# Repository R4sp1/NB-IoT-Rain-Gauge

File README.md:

# Návrh přesného srážkoměru s možností real-time odečtu

## Zadání
V teoretické části prostudujte principy měření objemu srážek. Prostudujte současné možnosti využití LPWAN sítí pro přenos naměřených hodnot. Na základě průzkumu dostupných řešení vyberte vhodnou metodu a měřicí modul pro přesné stanovení míry srážek. Současně vyberte vhodné komunikační řešení, které umožní real-time přenos naměřených hodnot. Výstupem semestrální práce je návrh a sestrojení zařízení pro přesné měření srážek s možností odesílání naměřených hodnot na server v reálném čase.

[Odkaz na práci](https://www.vut.cz/studenti/zav-prace/detail/151055 "Záverečné práce na VUT")

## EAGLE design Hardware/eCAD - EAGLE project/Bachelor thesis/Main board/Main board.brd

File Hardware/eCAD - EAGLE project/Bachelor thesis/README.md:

# eCAD files
This subfolder contains project files from EAGLE eCAD software. The main design is located in folder: [Main board](https://github.com/R4sp1/NB-IoT-Rain-Gauge/tree/main/Hardware/eCAD%20-%20EAGLE%20project/Bachelor%20thesis/Main%20board).

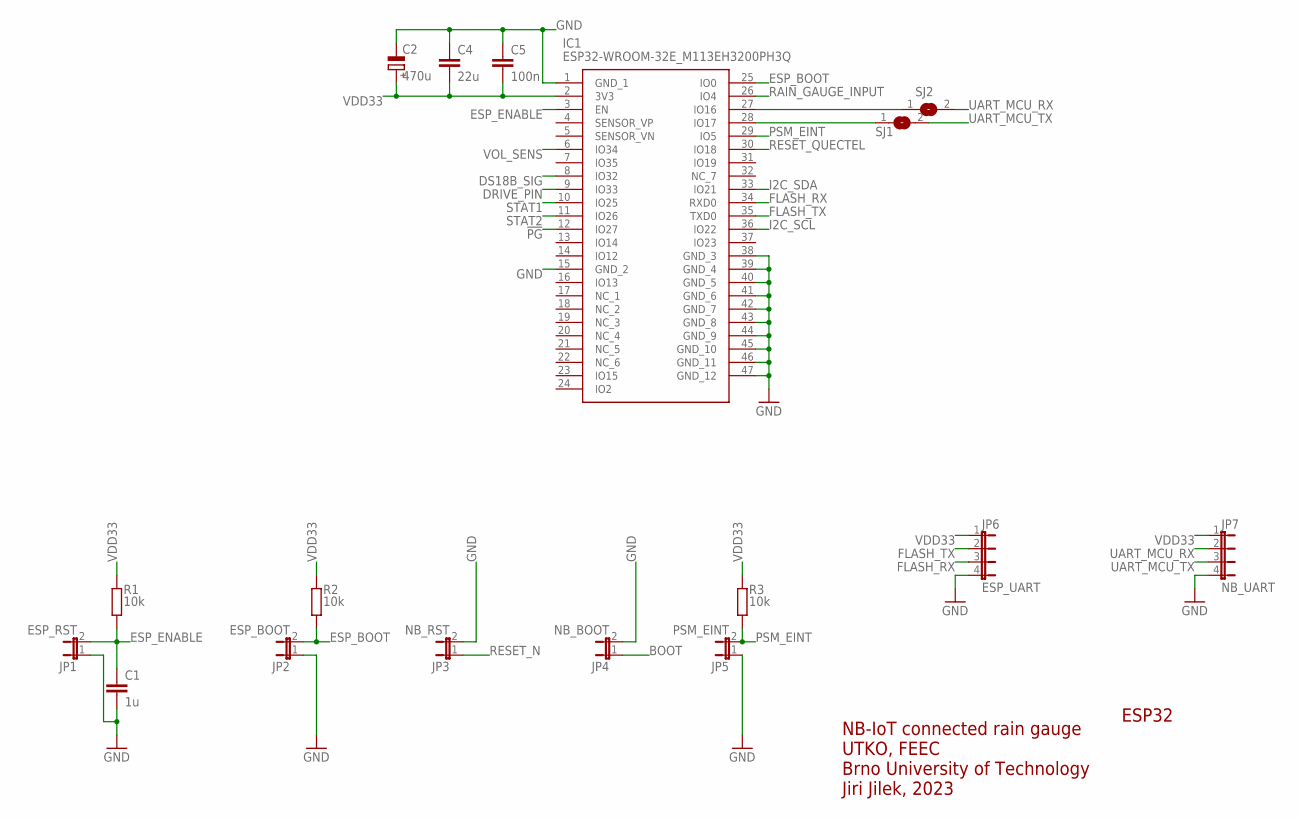
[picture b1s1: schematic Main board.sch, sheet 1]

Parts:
C1: 1u; C0603
C2: 470u; PANASONIC_D
C4: 22u; C0603
C5: 100n; C0603
IC1: ESP32-WROOM-32E_M113EH3200PH3Q; ESP32WROOM32EM113EH3200PH3Q0
JP1: ESP_RST; JP1
JP2: ESP_BOOT; JP1
JP3: NB_RST; JP1
JP4: NB_BOOT; JP1
JP5: PSM_EINT; JP1
JP6: ESP_UART; JP4
JP7: NB_UART; JP4
R1, R2, R3: 10k; R0603
SJ1, SJ2: SJ

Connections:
!PG: IC1.12 (IO27); also elsewhere on the board
BOOT: JP4.1; also elsewhere on the board
DRIVE_PIN: IC1.9 (IO33); also elsewhere on the board
DS18B_SIG: IC1.8 (IO32); also elsewhere on the board
ESP_BOOT: IC1.25 (IO0), JP2.2, R2.1
ESP_ENABLE: C1.1, IC1.3 (EN), JP1.2, R1.1
FLASH_RX: IC1.34 (RXD0), JP6.3
FLASH_TX: IC1.35 (TXD0), JP6.2
GND: C1.2, C2.-, C4.1, C5.1, IC1.1 (GND_1), IC1.15 (GND_2), IC1.38 (GND_3), IC1.39 (GND_4), IC1.40 (GND_5), IC1.41 (GND_6), IC1.42 (GND_7), IC1.43 (GND_8), IC1.44 (GND_9), IC1.45 (GND_10), IC1.46 (GND_11), IC1.47 (GND_12), JP1.1, JP2.1, JP3.2, JP4.2, JP5.1, JP6.4, JP7.4; also elsewhere on the board
I2C_SCL: IC1.36 (IO22); also elsewhere on the board
I2C_SDA: IC1.33 (IO21); also elsewhere on the board
unnamed: IC1.27 (IO16), SJ2.1
unnamed: IC1.28 (IO17), SJ1.1
PSM_EINT: IC1.29 (IO5), JP5.2, R3.1; also elsewhere on the board
RAIN_GAUGE_INPUT: IC1.26 (IO4); also elsewhere on the board
RESET_N: JP3.1; also elsewhere on the board
RESET_QUECTEL: IC1.30 (IO18); also elsewhere on the board
STAT1: IC1.10 (IO25); also elsewhere on the board
STAT2: IC1.11 (IO26); also elsewhere on the board
UART_MCU_RX: JP7.2, SJ2.2; also elsewhere on the board
UART_MCU_TX: JP7.3, SJ1.2; also elsewhere on the board
VDD33: C2.+, C4.2, C5.2, IC1.2 (3V3), JP6.1, JP7.1, R1.2, R2.2, R3.2; also elsewhere on the board
VOL_SENS: IC1.6 (IO34); also elsewhere on the board

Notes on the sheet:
ESP32
NB-IoT connected rain gauge UTKO, FEEC Brno University of Technology Jiri Jilek, 2023

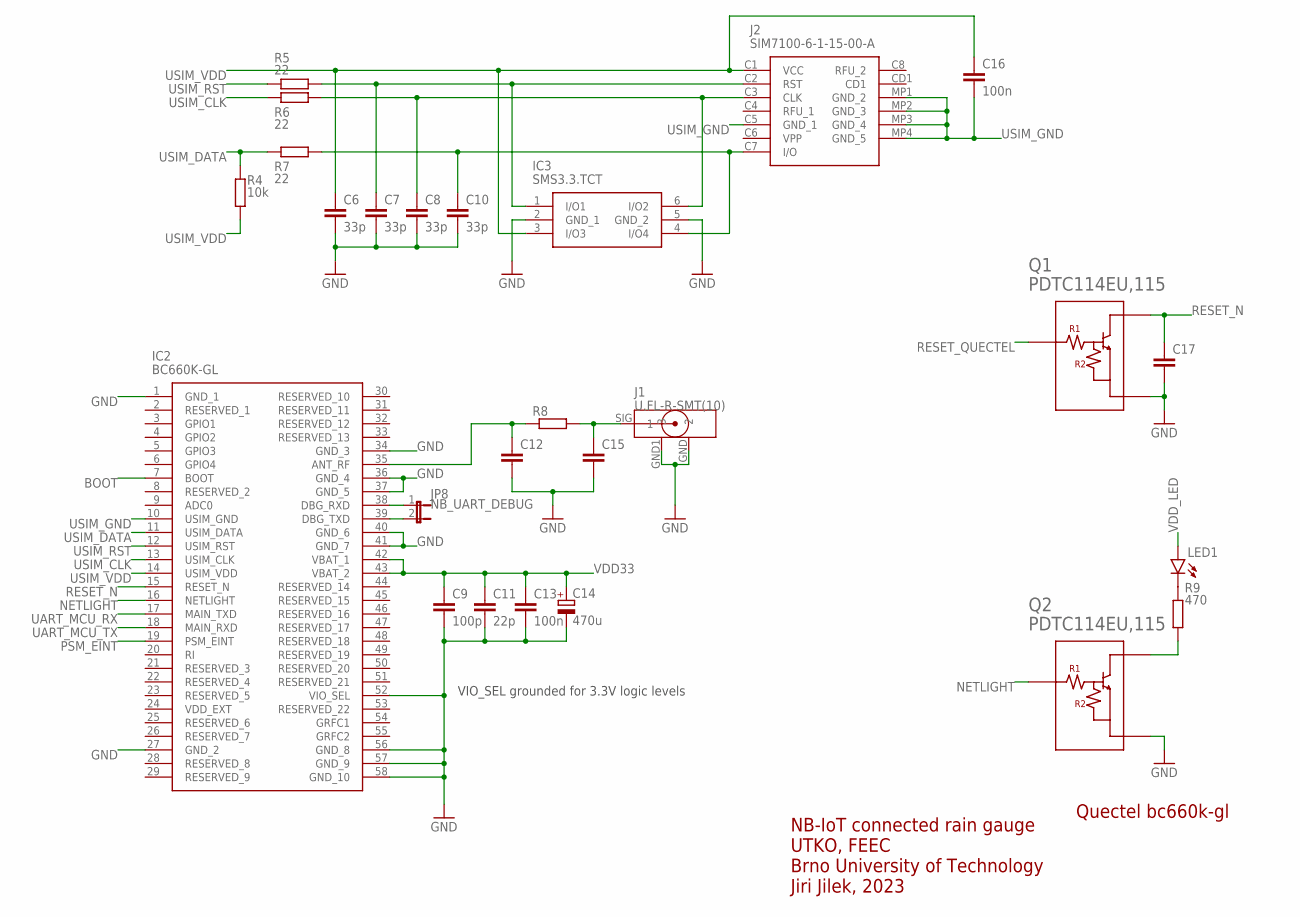
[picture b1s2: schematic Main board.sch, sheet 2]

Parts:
C6, C7, C8, C10: 33p; C0603
C9: 100p; C0603
C11: 22p; C0603
C12, C15, C17: C-EUC0603; C0603
C13, C16: 100n; C0603
C14: 470u; PANASONIC_D
IC2: BC660K-GL; BC660KGL
IC3: SMS3.3.TCT; SOT95P280X145-6N
J1: U.FL-R-SMT(10)
J2: SIM7100-6-1-15-00-A; SIM7100611500A
JP8: NB_UART_DEBUG; JP1
LED1: NETSTAT; CHIPLED_0805
Q1, Q2: PDTC114EU,115; SOT65P210X110-3N
R4: 10k; R0603
R5, R6, R7: 22; R0603
R8: R-EU_R0603; R0603
R9: 470; R0603

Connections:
BOOT: IC2.7 (BOOT); also elsewhere on the board
GND: C6.2, C7.2, C8.2, C9.2, C10.2, C11.2, C12.2, C13.2, C14.-, C15.2, C17.2, IC2.1 (GND_1), IC2.27 (GND_2), IC2.34 (GND_3), IC2.36 (GND_4), IC2.37 (GND_5), IC2.40 (GND_6), IC2.41 (GND_7), IC2.52 (VIO_SEL), IC2.56 (GND_8), IC2.57 (GND_9), IC2.58 (GND_10), IC3.2 (GND_1), IC3.5 (GND_2), J1.GND (2), J1.GND1 (3), Q1.2 (GND), Q2.2 (GND); also elsewhere on the board
unnamed: IC2.38 (DBG_RXD), JP8.1
unnamed: IC2.39 (DBG_TXD), JP8.2
unnamed: LED1.C, R9.2
unnamed: Q2.3 (OUTPUT), R9.1
unnamed: C12.1, IC2.35 (ANT_RF), R8.1
unnamed: C15.1, J1.SIG (1), R8.2
unnamed: C7.1, IC3.1 (I/O1), J2.C2 (RST), R5.2
unnamed: C8.1, IC3.6 (I/O2), J2.C3 (CLK), R6.2
unnamed: C10.1, IC3.4 (I/O4), J2.C7 (I/O), R7.2
NETLIGHT: IC2.16 (NETLIGHT), Q2.1 (INPUT)
PSM_EINT: IC2.19 (PSM_EINT); also elsewhere on the board
RESET_N: C17.1, IC2.15 (RESET_N), Q1.3 (OUTPUT); also elsewhere on the board
RESET_QUECTEL: Q1.1 (INPUT); also elsewhere on the board
UART_MCU_RX: IC2.17 (MAIN_TXD); also elsewhere on the board
UART_MCU_TX: IC2.18 (MAIN_RXD); also elsewhere on the board
USIM_CLK: IC2.13 (USIM_CLK), R6.1
USIM_DATA: IC2.11 (USIM_DATA), R4.2, R7.1
USIM_GND: C16.2, IC2.10 (USIM_GND), J2.C5 (GND_1), J2.MP1 (GND_2), J2.MP2 (GND_3), J2.MP3 (GND_4), J2.MP4 (GND_5)
USIM_RST: IC2.12 (USIM_RST), R5.1
USIM_VDD: C6.1, C16.1, IC2.14 (USIM_VDD), IC3.3 (I/O3), J2.C1 (VCC), R4.1
VDD33: C9.1, C11.1, C13.1, C14.+, IC2.42 (VBAT_1), IC2.43 (VBAT_2); also elsewhere on the board
VDD_LED: LED1.A; also elsewhere on the board

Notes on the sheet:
Quectel bc660k-gl
VIO_SEL grounded for 3.3V logic levels
NB-IoT connected rain gauge UTKO, FEEC Brno University of Technology Jiri Jilek, 2023

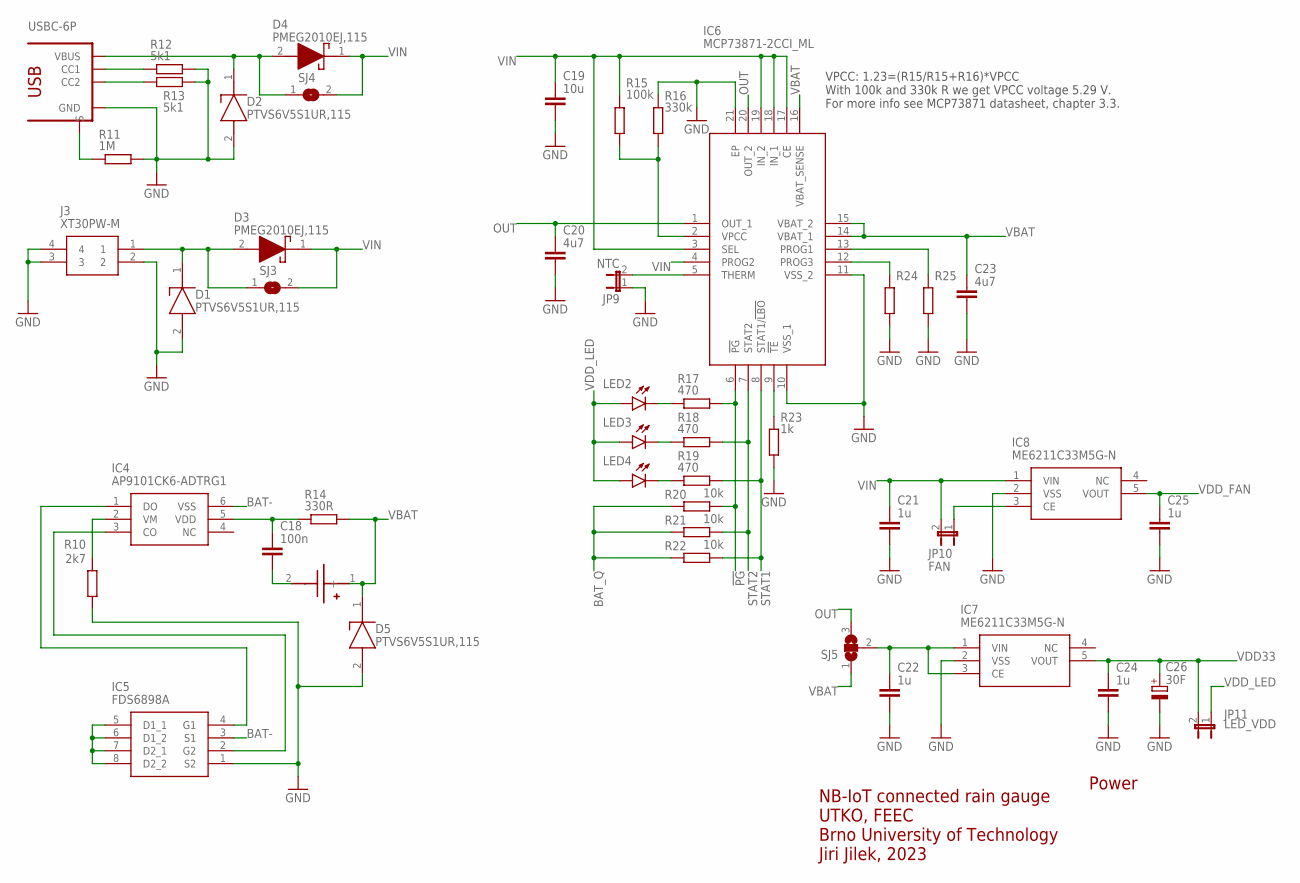
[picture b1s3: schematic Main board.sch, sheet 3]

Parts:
$3_29_$_2023-03-21_17-43-41: USBC-6P; USCX-06FX-XXMX-01
$3_30_$_2023-03-21_17-43-41: BLOSSOM-BLM-18650-1PCS
C18: 100n; C0603
C19: 10u; C0603
C20, C23: 4u7; C0603
C21, C22, C24, C25: 1u; C0603
C26: 30F; E5-10,5
D1, D2, D5: PTVS6V5S1UR,115; SOD123W
D3, D4: PMEG2010EJ,115; SODFL2512X80N
IC4: AP9101CK6-ADTRG1; SOT95P285X140-6N
IC5: FDS6898A; SOIC127P600X175-8N
IC6: MCP73871-2CCI_ML; QFN50P400X400X100-21N
IC7, IC8: ME6211C33M5G-N; SOT95P270X145-5N
J3: XT30PW-M; XT30PWM
JP9: NTC; JP1
JP10: FAN; JP1
JP11: LED_VDD; JP1
LED2: !PG; CHIPLED_0805
LED3: STAT2; CHIPLED_0805
LED4: STAT1; CHIPLED_0805
R10: 2k7; R0805
R11: 1M; R0603
R12, R13: 5k1; R0603
R14: 330R; R0603
R15: 100k; R0805
R16: 330k; R0805
R17, R18, R19: 470; R0603
R20, R21, R22: 10k; R0603
R23: 1k; R0603
R24, R25: R-EU_R0805; R0805
SJ3, SJ4: SJ
SJ5: SJ2W; SJ_2

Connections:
!PG: IC6.6 (!PG), R17.2, R20.2; also elsewhere on the board
!TE1: IC6.9 (!TE), R23.1
BAT-: $3_30_$_2023-03-21_17-43-41.2 (-), C18.2, IC4.6 (VSS), IC5.3 (S1)
BAT_Q: R20.1, R21.1, R22.1; also elsewhere on the board
CC3: $3_29_$_2023-03-21_17-43-41.CC2, R13.1
CC4: $3_29_$_2023-03-21_17-43-41.CC1, R12.1
DRAIN1: IC5.5 (D1_1), IC5.6 (D1_2), IC5.7 (D2_1), IC5.8 (D2_2)
G3: IC4.1 (DO), IC5.4 (G1)
G4: IC4.3 (CO), IC5.2 (G2)
GND: $3_29_$_2023-03-21_17-43-41.GND1 (GND), $3_29_$_2023-03-21_17-43-41.GND2 (GND), C19.2, C20.2, C21.2, C22.2, C23.2, C24.2, C25.2, C26.-, D1.2 (A), D2.2 (A), D5.2 (A), IC5.1 (S2), IC6.10 (VSS_1), IC6.11 (VSS_2), IC6.21 (EP), IC7.2 (VSS), IC8.2 (VSS), J3.2, J3.3, J3.4, JP9.1, R10.1, R11.2, R12.2, R13.2, R16.2, R23.2, R24.2, R25.2; also elsewhere on the board
unnamed: C18.1, IC4.5 (VDD), R14.1
unnamed: IC8.3 (CE), JP10.1
unnamed: LED2.C, R17.1
unnamed: LED3.C, R18.1
unnamed: LED4.C, R19.1
OUT: C20.1, IC6.1 (OUT_1), IC6.20 (OUT_2), SJ5.3
PROG1: IC6.13 (PROG1), R25.1
PROG3: IC6.12 (PROG3), R24.1
PV_IN1: D1.1 (K), D3.2 (A), J3.1, SJ3.1
S1: $3_29_$_2023-03-21_17-43-41.SHIELD1 (S), $3_29_$_2023-03-21_17-43-41.SHIELD2 (S), $3_29_$_2023-03-21_17-43-41.SHIELD3 (S), $3_29_$_2023-03-21_17-43-41.SHIELD4 (S), R11.1
STAT1: IC6.8 (STAT1/!LBO), R19.2, R22.2; also elsewhere on the board
STAT2: IC6.7 (STAT2), R18.2, R21.2; also elsewhere on the board
THERM1: IC6.5 (THERM), JP9.2
VBAT: $3_30_$_2023-03-21_17-43-41.1 (+), C23.1, D5.1 (K), IC6.14 (VBAT_1), IC6.15 (VBAT_2), IC6.16 (VBAT_SENSE), R14.2, SJ5.1; also elsewhere on the board
VBUS1: $3_29_$_2023-03-21_17-43-41.VBUS1 (VBUS), $3_29_$_2023-03-21_17-43-41.VBUS2 (VBUS), D2.1 (K), D4.2 (A), SJ4.1
VDD33: C24.1, C26.+, IC7.5 (VOUT), JP11.2; also elsewhere on the board
VDD_FAN: C25.1, IC8.5 (VOUT); also elsewhere on the board
VDD_LED: JP11.1, LED2.A, LED3.A, LED4.A; also elsewhere on the board
VIN: C19.1, C21.1, D3.1 (K), D4.1 (K), IC6.3 (SEL), IC6.4 (PROG2), IC6.17 (CE), IC6.18 (IN_1), IC6.19 (IN_2), IC8.1 (VIN), JP10.2, R15.2, SJ3.2, SJ4.2
VIN_LDO: C22.1, IC7.1 (VIN), IC7.3 (CE), SJ5.2
VM1: IC4.2 (VM), R10.2
VPCC1: IC6.2 (VPCC), R15.1, R16.1

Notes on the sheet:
Power
VPCC: 1.23=(R15/R15+R16)*VPCC With 100k and 330k R we get VPCC voltage 5.29 V. For more info see MCP73871 datasheet, chapter 3.3.
NB-IoT connected rain gauge UTKO, FEEC Brno University of Technology Jiri Jilek, 2023

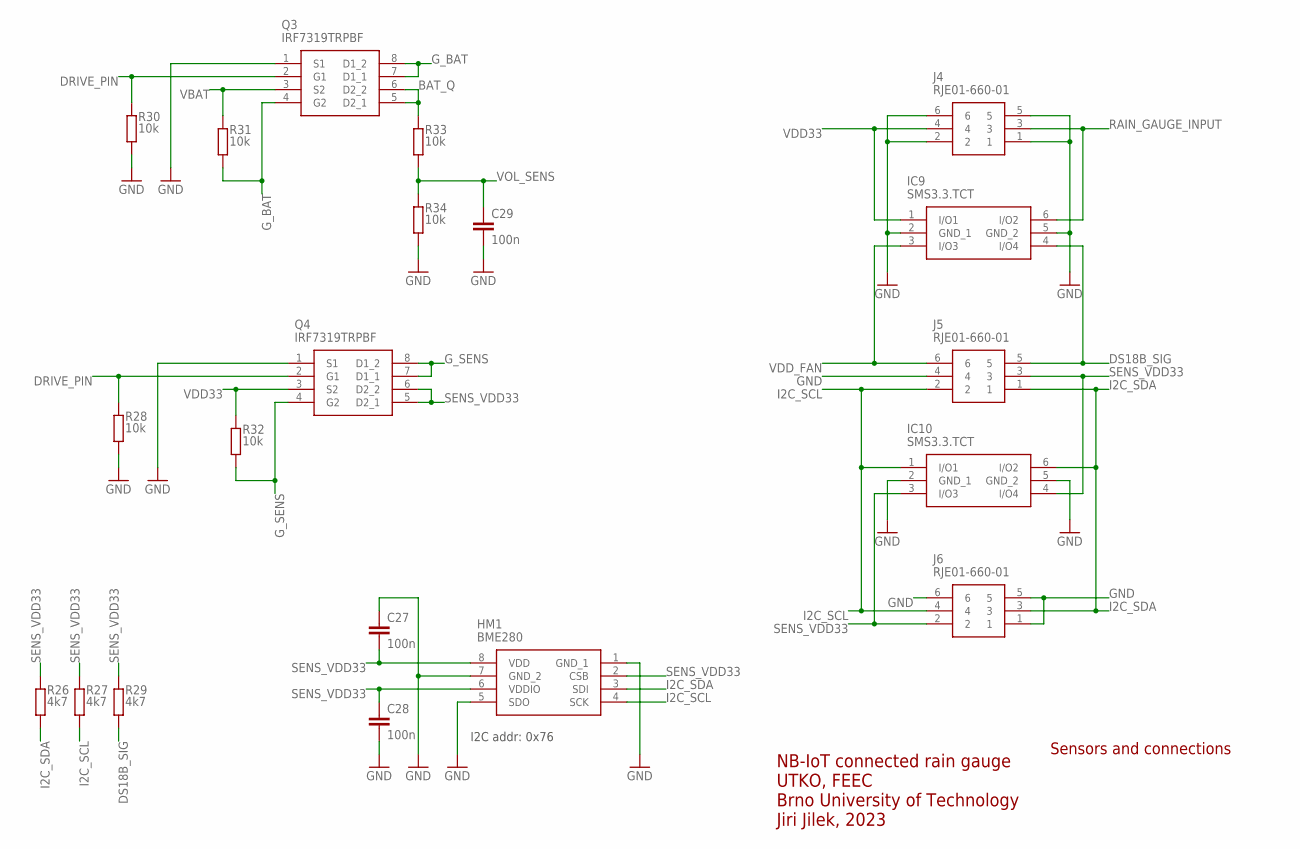
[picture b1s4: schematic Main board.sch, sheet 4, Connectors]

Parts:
C27, C28, C29: 100n; C0805
HM1: BME280
IC9, IC10: SMS3.3.TCT; SOT95P280X145-6N
J4, J5, J6: RJE01-660-01; RJE0166001
Q3, Q4: IRF7319TRPBF; SOIC127P600X175-8N
R26, R27, R29: 4k7; R0805
R28, R30, R31, R32, R33, R34: 10k; R0805

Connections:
BAT_Q: Q3.5 (D2_1), Q3.6 (D2_2), R33.2; also elsewhere on the board
DRIVE_PIN: Q3.2 (G1), Q4.2 (G1), R28.2, R30.2; also elsewhere on the board
DS18B_SIG: IC9.4 (I/O4), J5.5, R29.1; also elsewhere on the board
GND: C27.1, C28.2, C29.2, HM1.1 (GND_1), HM1.5 (SDO), HM1.7 (GND_2), IC9.2 (GND_1), IC9.5 (GND_2), IC10.2 (GND_1), IC10.5 (GND_2), J4.1, J4.2, J4.5, J4.6, J5.4, J6.1, J6.5, J6.6, Q3.1 (S1), Q4.1 (S1), R28.1, R30.1, R34.1; also elsewhere on the board
G_BAT: Q3.4 (G2), Q3.7 (D1_1), Q3.8 (D1_2), R31.2
G_SENS: Q4.4 (G2), Q4.7 (D1_1), Q4.8 (D1_2), R32.2
I2C_SCL: HM1.4 (SCK), IC10.1 (I/O1), J5.2, J6.4, R27.1; also elsewhere on the board
I2C_SDA: HM1.3 (SDI), IC10.6 (I/O2), J5.1, J6.3, R26.1; also elsewhere on the board
RAIN_GAUGE_INPUT: IC9.6 (I/O2), J4.3; also elsewhere on the board
SENS_VDD33: C27.2, C28.1, HM1.2 (CSB), HM1.6 (VDDIO), HM1.8 (VDD), IC10.3 (I/O3), IC10.4 (I/O4), J5.3, J6.2, Q4.5 (D2_1), Q4.6 (D2_2), R26.2, R27.2, R29.2
VBAT: Q3.3 (S2), R31.1; also elsewhere on the board
VDD33: IC9.1 (I/O1), J4.4, Q4.3 (S2), R32.1; also elsewhere on the board
VDD_FAN: IC9.3 (I/O3), J5.6; also elsewhere on the board
VOL_SENS: C29.1, R33.1, R34.2; also elsewhere on the board

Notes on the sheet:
Sensors and connections
I2C addr: 0x76
NB-IoT connected rain gauge UTKO, FEEC Brno University of Technology Jiri Jilek, 2023

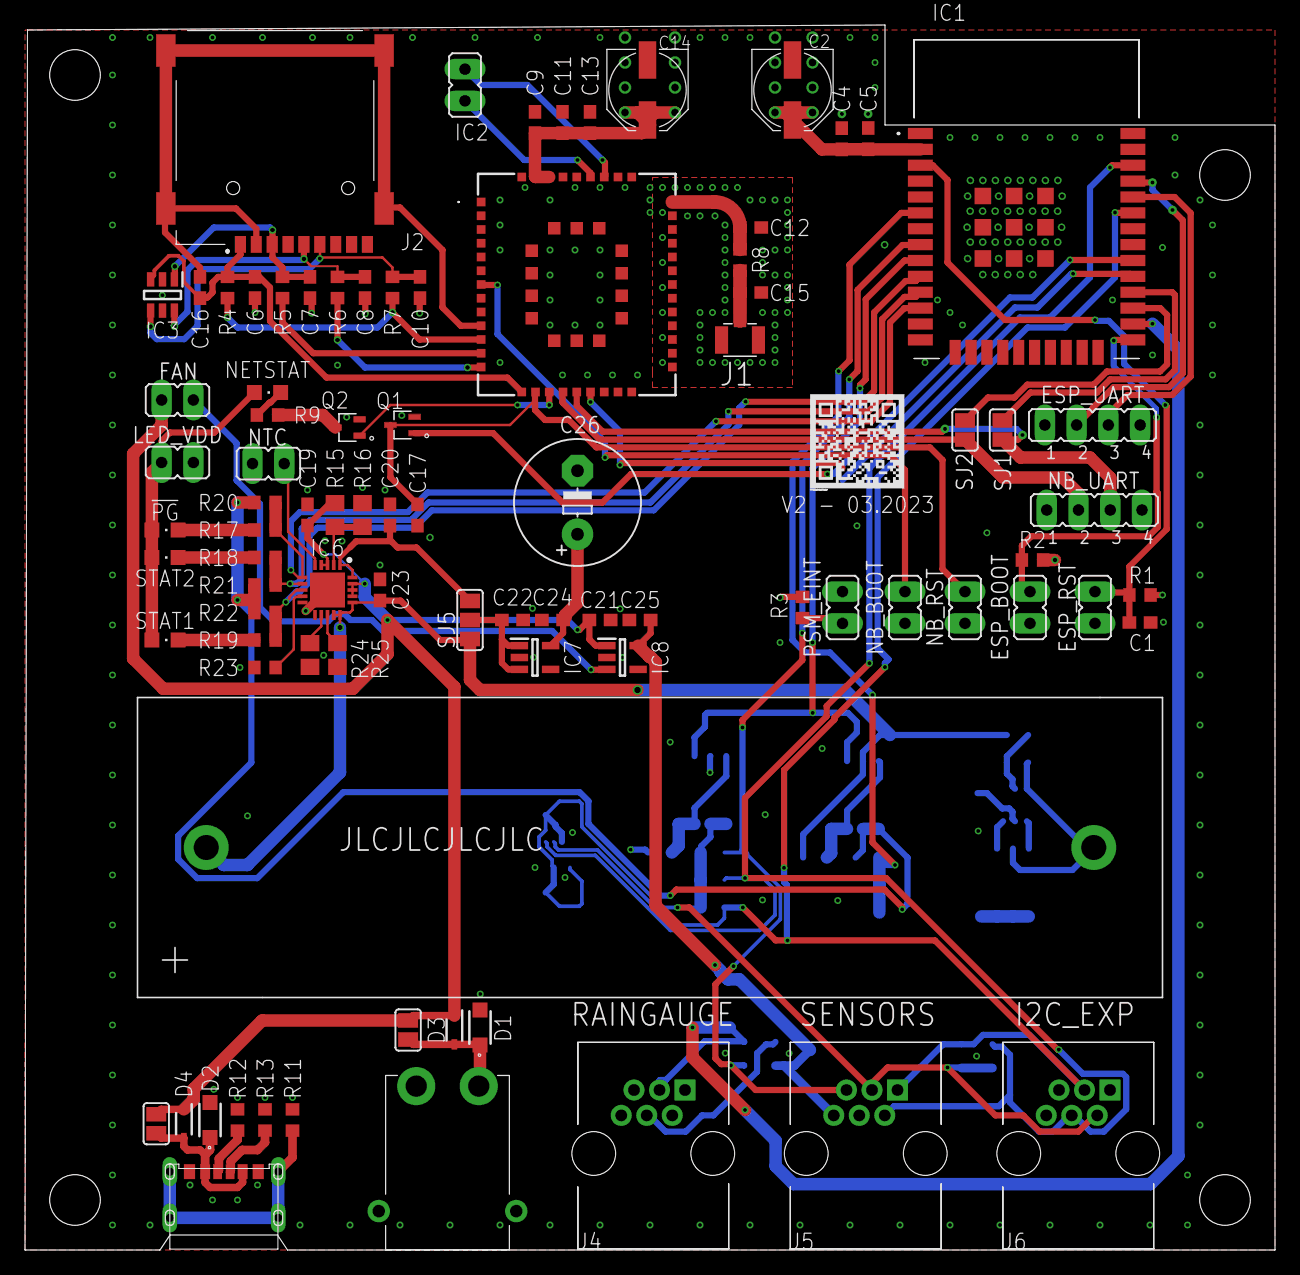
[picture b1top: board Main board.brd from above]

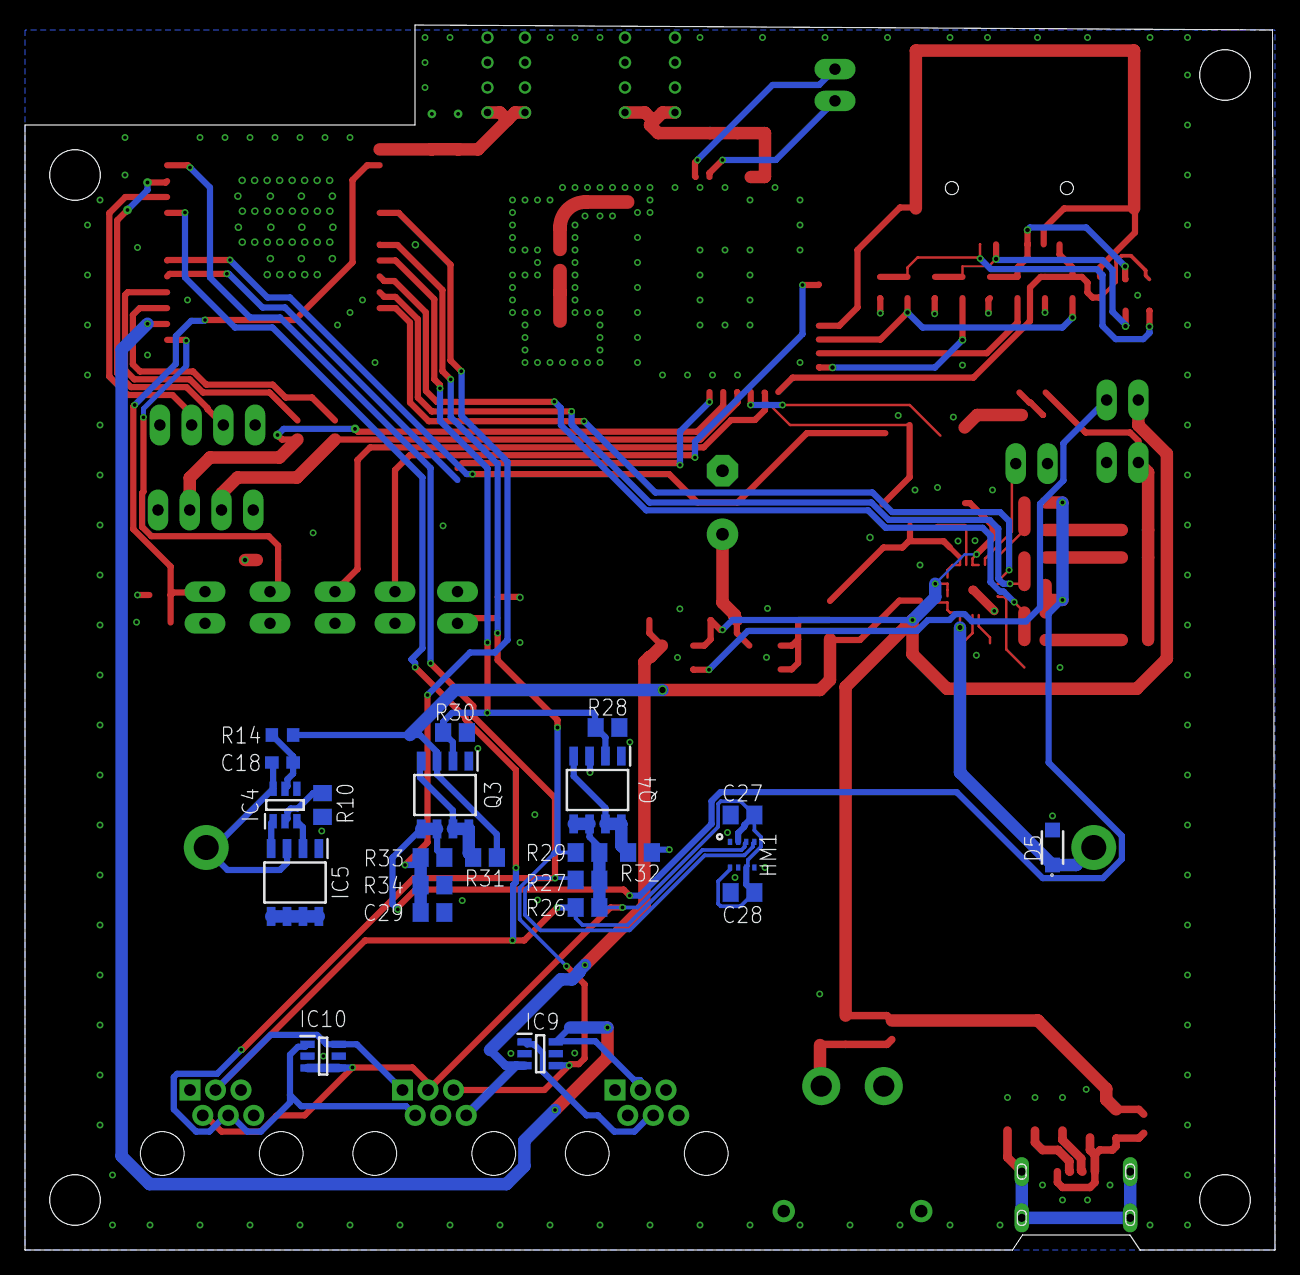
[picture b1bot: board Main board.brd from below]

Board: 4 copper layers, 100.0 x 98.0 mm, 110 parts (23 on the bottom side), 68 nets.

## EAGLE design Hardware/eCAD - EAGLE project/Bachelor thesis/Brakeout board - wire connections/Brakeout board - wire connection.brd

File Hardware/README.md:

# Hardware folder
This folder contains all hardware design/manufacture files.

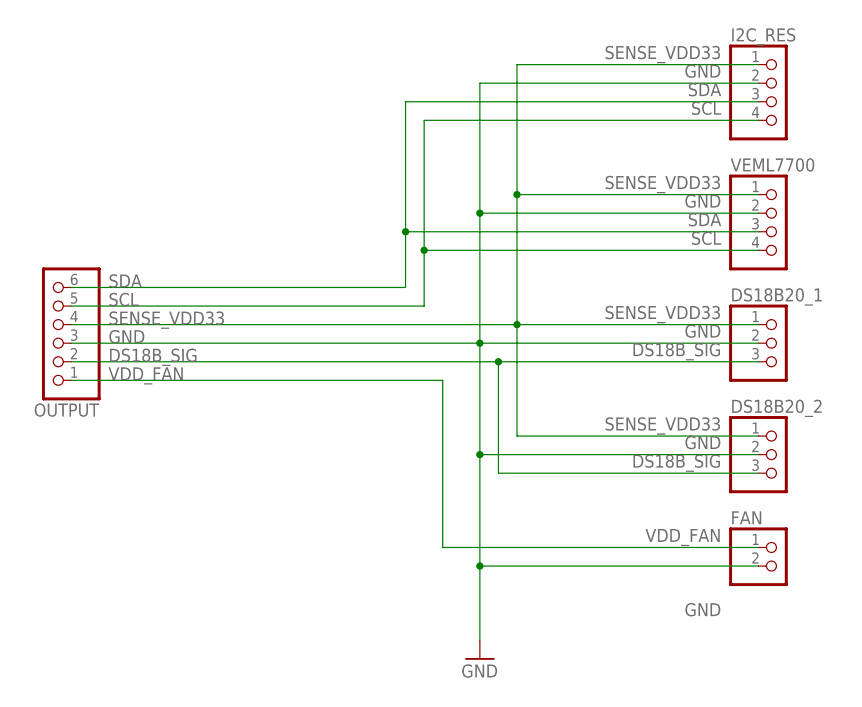
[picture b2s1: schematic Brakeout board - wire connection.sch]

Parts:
DS18B20_1, DS18B20_2: PINHD-1X3; 1X03
FAN: PINHD-1X2; 1X02
I2C_RES: PINHD-1X4; 1X04
OUTPUT: PINHD-1X6; 1X06
VEML7700: PINHD-1X4; 1X04

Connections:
DS18B_SIG: DS18B20_1.3, DS18B20_2.3, OUTPUT.2
GND: DS18B20_1.2, DS18B20_2.2, FAN.2, I2C_RES.2, OUTPUT.3, VEML7700.2
SCL: I2C_RES.4, OUTPUT.5, VEML7700.4
SDA: I2C_RES.3, OUTPUT.6, VEML7700.3
SENSE_VDD33: DS18B20_1.1, DS18B20_2.1, I2C_RES.1, OUTPUT.4, VEML7700.1
VDD_FAN: FAN.1, OUTPUT.1

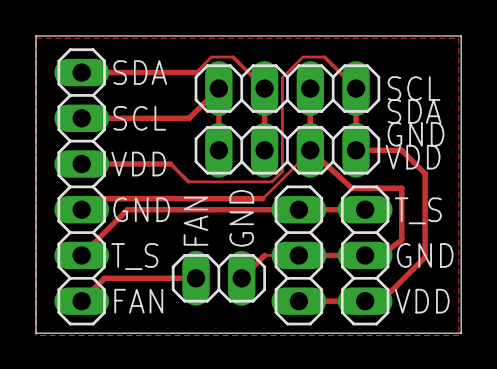
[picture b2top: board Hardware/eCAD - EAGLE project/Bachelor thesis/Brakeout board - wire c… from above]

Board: 2 copper layers, 23.6 x 16.5 mm, 6 parts (0 on the bottom side), 6 nets.

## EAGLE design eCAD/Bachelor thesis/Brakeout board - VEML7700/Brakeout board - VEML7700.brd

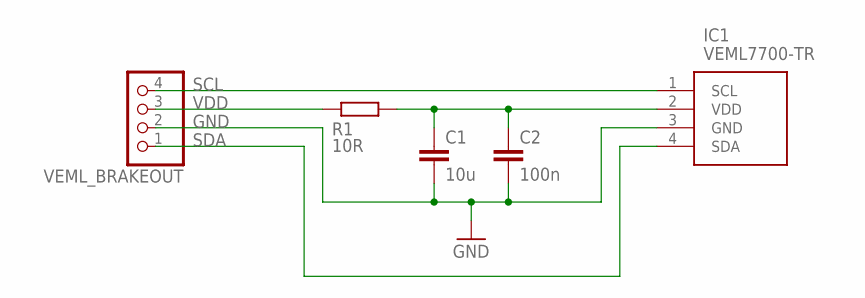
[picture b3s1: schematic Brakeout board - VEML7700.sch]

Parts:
C1: 10u; C0603
C2: 100n; C0603
IC1: VEML7700-TR; VEML7700
R1: 10R; R0603
VEML_BRAKEOUT: PINHD-1X4; 1X04

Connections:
GND: C1.2, C2.2, IC1.3 (GND), VEML_BRAKEOUT.2
unnamed: C1.1, C2.1, IC1.2 (VDD), R1.2
SCL: IC1.1 (SCL), VEML_BRAKEOUT.4
SDA: IC1.4 (SDA), VEML_BRAKEOUT.1
VDD: R1.1, VEML_BRAKEOUT.3

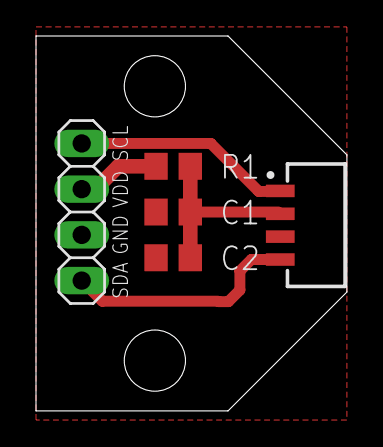
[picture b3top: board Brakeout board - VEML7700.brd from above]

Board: 2 copper layers, 17.3 x 20.8 mm, 5 parts (0 on the bottom side), 5 nets.

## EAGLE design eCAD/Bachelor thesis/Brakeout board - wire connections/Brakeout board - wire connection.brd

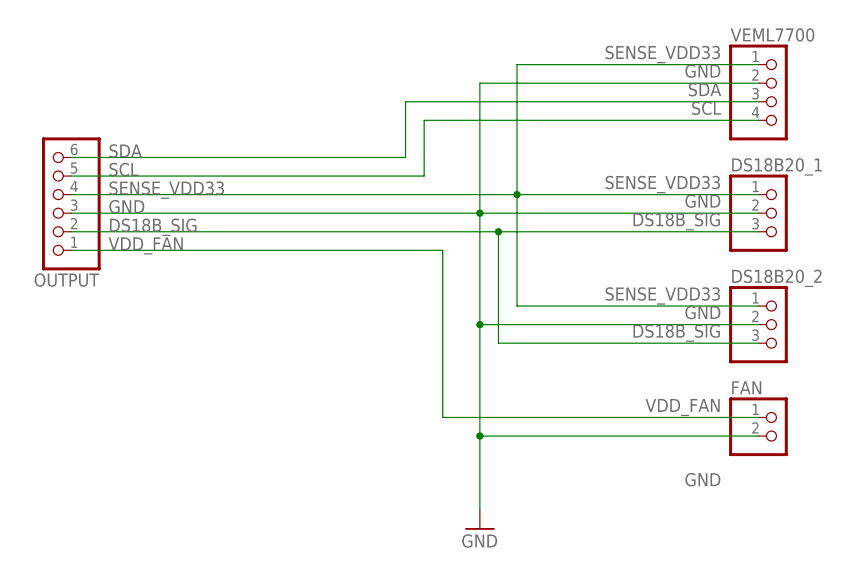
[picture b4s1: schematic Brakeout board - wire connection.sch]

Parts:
DS18B20_1, DS18B20_2: PINHD-1X3; 1X03
FAN: PINHD-1X2; 1X02
OUTPUT: PINHD-1X6; 1X06
VEML7700: PINHD-1X4; 1X04

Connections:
DS18B_SIG: DS18B20_1.3, DS18B20_2.3, OUTPUT.2
GND: DS18B20_1.2, DS18B20_2.2, FAN.2, OUTPUT.3, VEML7700.2
SCL: OUTPUT.5, VEML7700.4
SDA: OUTPUT.6, VEML7700.3
SENSE_VDD33: DS18B20_1.1, DS18B20_2.1, OUTPUT.4, VEML7700.1
VDD_FAN: FAN.1, OUTPUT.1

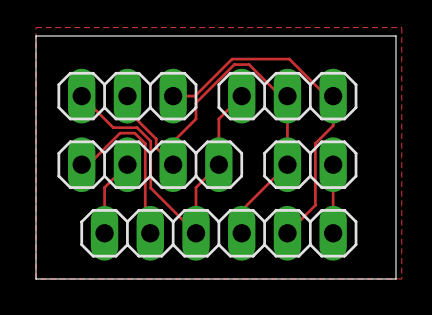
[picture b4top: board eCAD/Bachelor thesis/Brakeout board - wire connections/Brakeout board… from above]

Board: 2 copper layers, 20.0 x 13.5 mm, 5 parts (0 on the bottom side), 6 nets.

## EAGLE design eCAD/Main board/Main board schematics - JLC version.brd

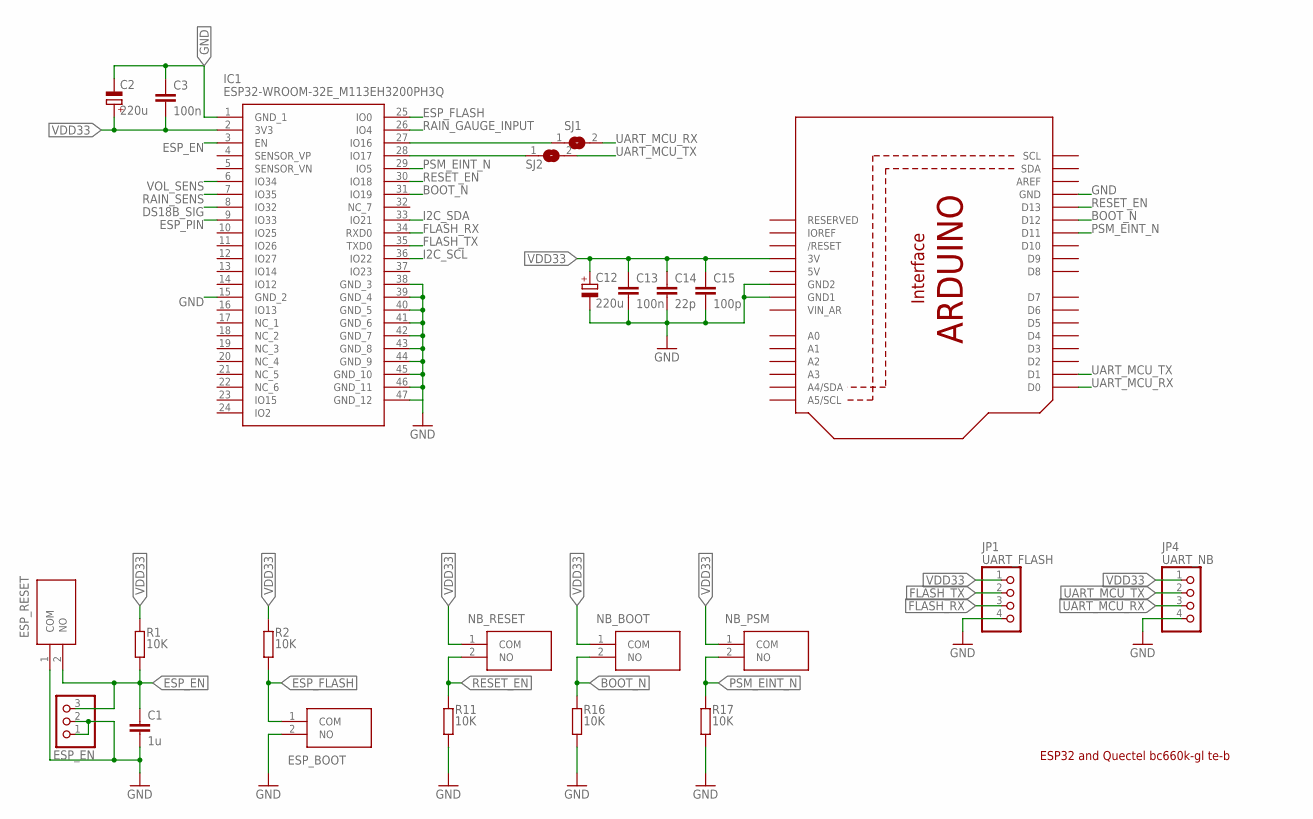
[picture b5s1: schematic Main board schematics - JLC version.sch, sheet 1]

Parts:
C1: 1u; C0805
C2, C12: 220u; PANASONIC_D
C3, C13: 100n; C0805
C14: 22p; C0805
C15: 100p; C0805
ESP_BOOT: TS-1088-AR02016; TS1088AR02016
ESP_EN: PINHD-1X3; 1X03
ESP_RESET: TS-1088-AR02016; TS1088AR02016
IC1: ESP32-WROOM-32E_M113EH3200PH3Q; ESP32WROOM32EM113EH3200PH3Q0
JP1: UART_FLASH; 1X04
JP4: UART_NB; 1X04
NB_BOOT: TS-1088-AR02016; TS1088AR02016
NB_PSM: TS-1088-AR02016; TS1088AR02016
NB_RESET: TS-1088-AR02016; TS1088AR02016
R1, R2, R11, R16, R17: 10K; R0805
SJ1, SJ2: SJ
U1: ARDUINOR3-BPLACE; ARDUINOR3

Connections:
5V: U1.5V
BOOT_N: IC1.31 (IO19), NB_BOOT.2 (NO), R16.2, U1.D12
DS18B_SIG: IC1.8 (IO32); also elsewhere on the board
ESP_EN: C1.1, ESP_EN.3, ESP_RESET.2 (NO), IC1.3 (EN), R1.1
ESP_FLASH: ESP_BOOT.1 (COM), IC1.25 (IO0), R2.1
ESP_PIN: IC1.9 (IO33); also elsewhere on the board
FLASH_RX: IC1.34 (RXD0), JP1.3
FLASH_TX: IC1.35 (TXD0), JP1.2
GND: C1.2, C2.-, C3.1, C12.-, C13.2, C14.2, C15.2, ESP_BOOT.2 (NO), ESP_EN.1, ESP_EN.2, ESP_RESET.1 (COM), IC1.1 (GND_1), IC1.15 (GND_2), IC1.38 (GND_3), IC1.39 (GND_4), IC1.40 (GND_5), IC1.41 (GND_6), IC1.42 (GND_7), IC1.43 (GND_8), IC1.44 (GND_9), IC1.45 (GND_10), IC1.46 (GND_11), IC1.47 (GND_12), JP1.4, JP4.4, R11.1, R16.1, R17.1, U1.D14 (GND), U1.GND, U1.GND1, U1.GND2; also elsewhere on the board
I2C_SCL: IC1.36 (IO22); also elsewhere on the board
I2C_SDA: IC1.33 (IO21); also elsewhere on the board
unnamed: IC1.27 (IO16), SJ1.1
unnamed: IC1.28 (IO17), SJ2.1
PSM_EINT_N: IC1.29 (IO5), NB_PSM.2 (NO), R17.2, U1.D11
RAIN_GAUGE_INPUT: IC1.26 (IO4); also elsewhere on the board
RAIN_SENS: IC1.7 (IO35)
RESET_EN: IC1.30 (IO18), NB_RESET.2 (NO), R11.2, U1.D13
UART_MCU_RX: JP4.3, SJ1.2, U1.D0
UART_MCU_TX: JP4.2, SJ2.2, U1.D1
VDD33: C2.+, C3.2, C12.+, C13.1, C14.1, C15.1, IC1.2 (3V3), JP1.1, JP4.1, NB_BOOT.1 (COM), NB_PSM.1 (COM), NB_RESET.1 (COM), R1.2, R2.2, U1.VBAT (3V); also elsewhere on the board
VIN_AR: U1.VIN_AR
VOL_SENS: IC1.6 (IO34); also elsewhere on the board

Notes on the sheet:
ESP32 and Quectel bc660k-gl te-b

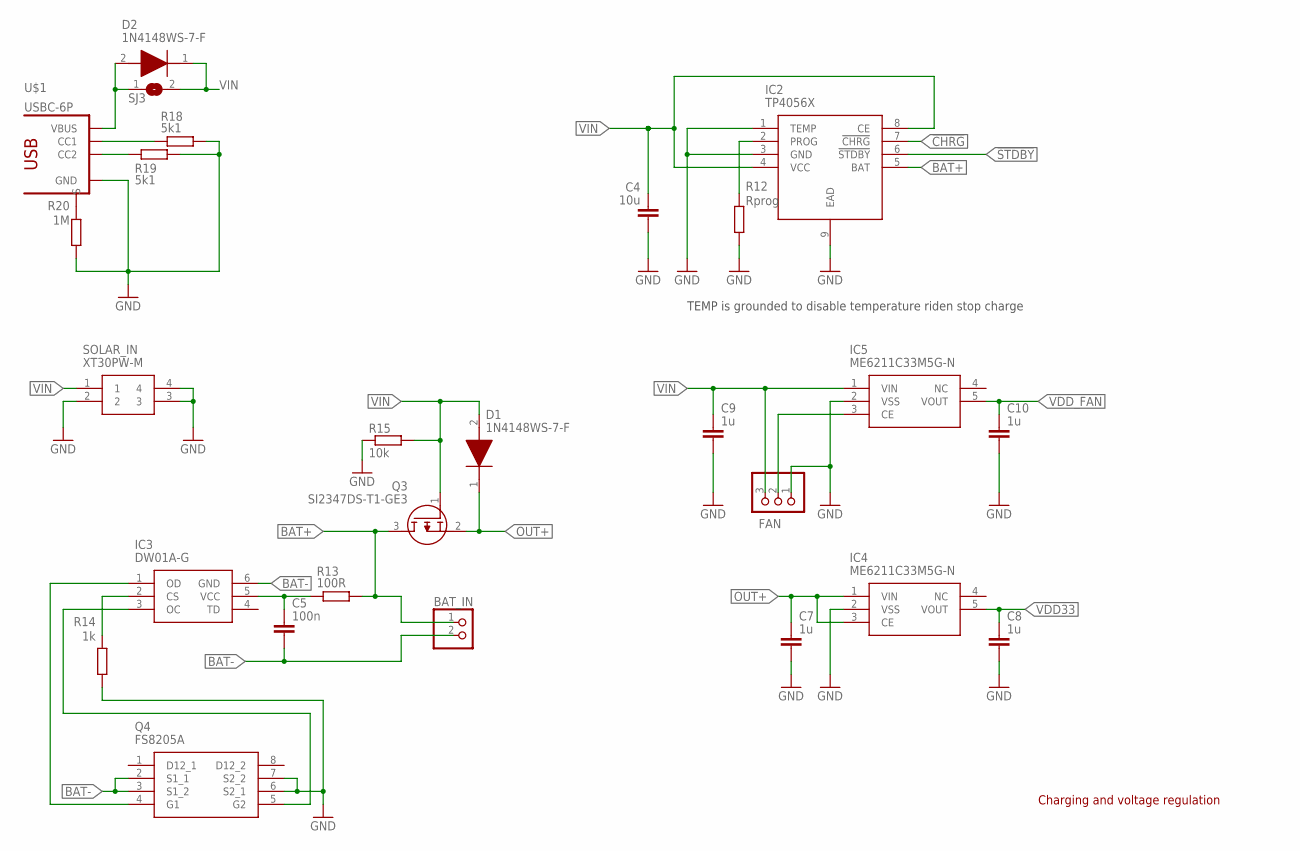
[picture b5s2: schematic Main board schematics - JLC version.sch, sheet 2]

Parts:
BAT_IN: PINHD-1X2; 1X02
C4: 10u; C0805
C5: 100n; C0805
C7, C8, C9, C10: 1u; C0805
D1, D2: 1N4148WS-7-F; SOD2513X120N
FAN: PINHD-1X3; 1X03
IC2: TP4056X; SOIC127P600X175-9N
IC3: DW01A-G; SOT95P280X135-6N
IC4, IC5: ME6211C33M5G-N; SOT95P270X145-5N
Q3: SI2347DS-T1-GE3; SOT95P237X112-3N
Q4: FS8205A; SOP65P640X120-8N
R12: Rprog; R0805
R13: 100R; R0805
R14: 1k; R0805
R15: 10k; R0805
R18, R19: 5k1; R0805
R20: 1M; R0805
SJ3: SJ
SOLAR_IN: XT30PW-M; XT30PWM
U$1: USBC-6P; USCX-06FX-XXMX-01

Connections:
!CHRG: IC2.7 (!CHRG)
!STDBY: IC2.6 (!STDBY)
BAT+: BAT_IN.1, IC2.5 (BAT), Q3.3 (D), R13.2; also elsewhere on the board
BAT-: BAT_IN.2, C5.2, IC3.6 (GND), Q4.2 (S1_1), Q4.3 (S1_2)
GND: C4.2, C7.2, C8.2, C9.2, C10.2, FAN.1, IC2.1 (TEMP), IC2.3 (GND), IC2.9 (EAD), IC4.2 (VSS), IC5.2 (VSS), Q4.6 (S2_1), Q4.7 (S2_2), R12.2, R14.1, R15.1, R18.1, R19.1, R20.2, SOLAR_IN.2, SOLAR_IN.3, SOLAR_IN.4, U$1.GND1 (GND), U$1.GND2 (GND); also elsewhere on the board
unnamed: IC2.2 (PROG), R12.1
unnamed: D2.2 (A), SJ3.1, U$1.VBUS1 (VBUS), U$1.VBUS2 (VBUS)
unnamed: FAN.2, IC5.3 (CE)
unnamed: C5.1, IC3.5 (VCC), R13.1
unnamed: R20.1, U$1.SHIELD1 (S), U$1.SHIELD2 (S), U$1.SHIELD3 (S), U$1.SHIELD4 (S)
unnamed: IC3.2 (CS), R14.2
unnamed: IC3.1 (OD), Q4.4 (G1)
unnamed: R19.2, U$1.CC2
unnamed: IC3.3 (OC), Q4.5 (G2)
unnamed: R18.2, U$1.CC1
OUT+: C7.1, D1.1 (K), IC4.1 (VIN), IC4.3 (CE), Q3.2 (S)
VDD33: C8.1, IC4.5 (VOUT); also elsewhere on the board
VDD_FAN: C10.1, IC5.5 (VOUT); also elsewhere on the board
VIN: C4.1, C9.1, D1.2 (A), D2.1 (K), FAN.3, IC2.4 (VCC), IC2.8 (CE), IC5.1 (VIN), Q3.1 (G), R15.2, SJ3.2, SOLAR_IN.1

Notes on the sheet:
Charging and voltage regulation
TEMP is grounded to disable temperature riden stop charge

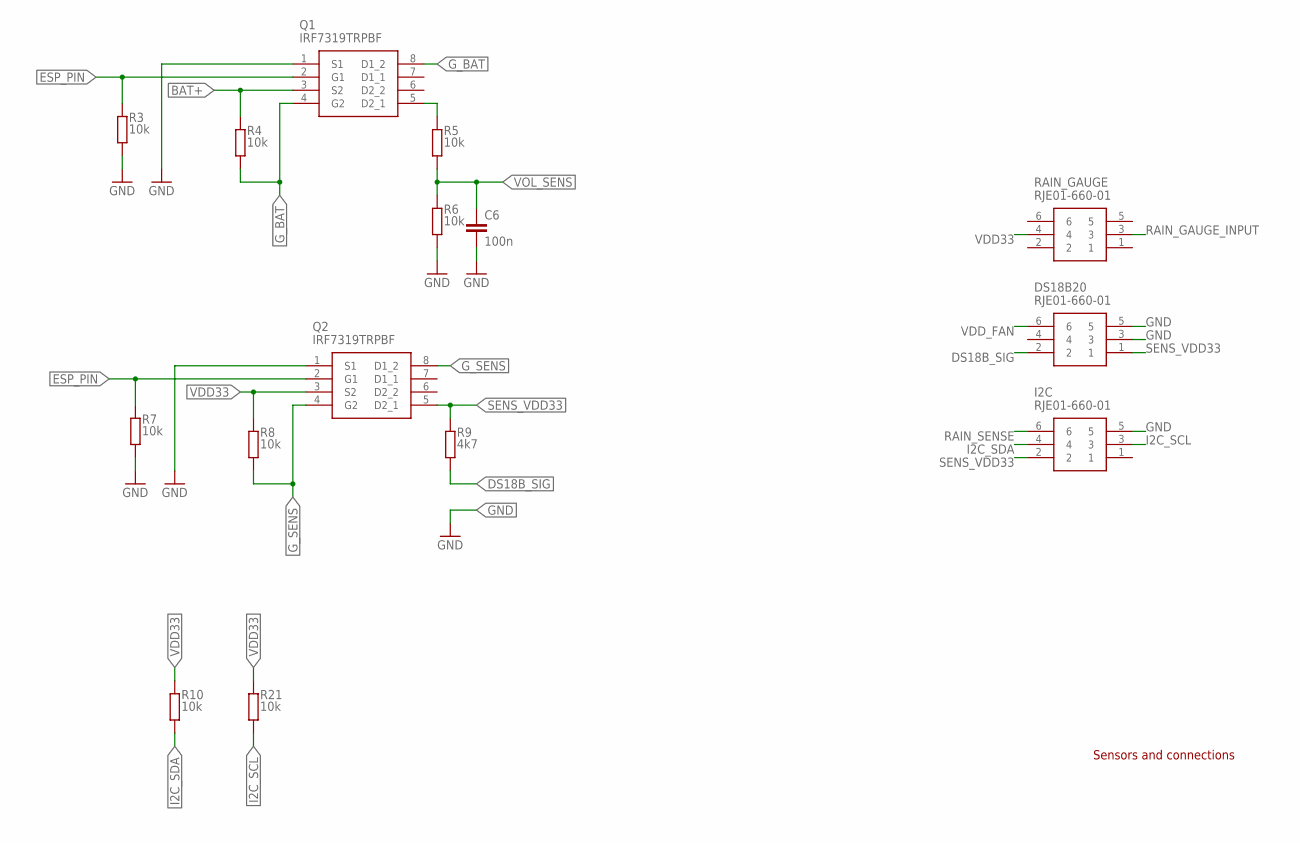
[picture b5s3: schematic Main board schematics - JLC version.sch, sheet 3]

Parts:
C6: 100n; C0805
DS18B20: RJE01-660-01; RJE0166001
I2C: RJE01-660-01; RJE0166001
Q1, Q2: IRF7319TRPBF; SOIC127P600X175-8N
R3, R4, R5, R6, R7, R8, R10, R21: 10k; R0805
R9: 4k7; R0805
RAIN_GAUGE: RJE01-660-01; RJE0166001

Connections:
BAT+: Q1.3 (S2), R4.1; also elsewhere on the board
DS18B_SIG: DS18B20.2, R9.1; also elsewhere on the board
ESP_PIN: Q1.2 (G1), Q2.2 (G1), R3.2, R7.2; also elsewhere on the board
GND: C6.2, DS18B20.3, DS18B20.5, I2C.5, Q1.1 (S1), Q2.1 (S1), R3.1, R6.1, R7.1; also elsewhere on the board
G_BAT: Q1.4 (G2), Q1.8 (D1_2), R4.2
G_SENS: Q2.4 (G2), Q2.8 (D1_2), R8.2
I2C_SCL: I2C.3, R21.1; also elsewhere on the board
I2C_SDA: I2C.4, R10.1; also elsewhere on the board
unnamed: Q1.5 (D2_1), R5.2
RAIN_GAUGE_INPUT: RAIN_GAUGE.3; also elsewhere on the board
RAIN_SENSE: I2C.6
SENS_VDD33: DS18B20.1, I2C.2, Q2.5 (D2_1), R9.2
VDD33: Q2.3 (S2), R8.1, R10.2, R21.2, RAIN_GAUGE.4; also elsewhere on the board
VDD_FAN: DS18B20.6; also elsewhere on the board
VOL_SENS: C6.1, R5.1, R6.2; also elsewhere on the board

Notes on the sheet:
Sensors and connections
